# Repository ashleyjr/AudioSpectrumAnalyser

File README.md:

AudioSpectrumAnalyser
=====================

20Hz - 20KHz spectrum analyser which will eventually be part of hi-fi system. Processing on a beefy microcontroller and a small display with spectrum grpah.

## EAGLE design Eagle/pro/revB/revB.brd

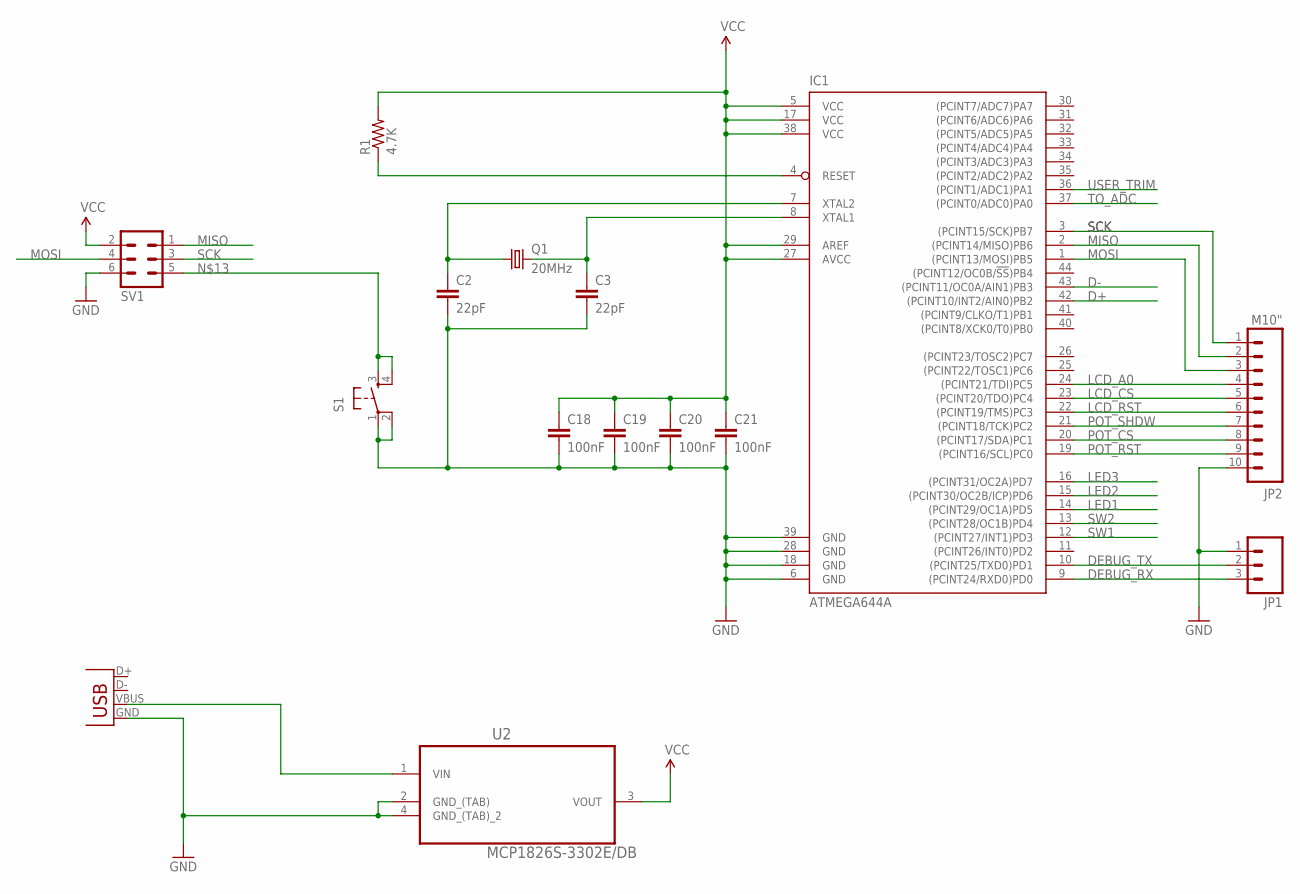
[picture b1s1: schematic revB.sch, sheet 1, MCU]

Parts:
C2, C3: 22pF; 0805
C18, C19, C20, C21: 100nF; 0805
IC1: ATMEGA644A; TQFP44
JP1: M03PTH; 1X03
JP2: M10"; 1X10
Q1: 20MHz; HC49U-V
R1: 4.7K; 1206
S1: TAC_SWITCHPTH; TACTILE-PTH
SV1: MA03-2
U2: MCP1826S-3302E/DB; SOT230P700X180-4N
X2: USB-MB-H

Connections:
D+: IC1.42 ((PCINT10/INT2/AIN0)PB2)
D-: IC1.43 ((PCINT11/OC0A/AIN1)PB3)
DEBUG_RX: IC1.9 ((PCINT24/RXD0)PD0), JP1.3
DEBUG_TX: IC1.10 ((PCINT25/TXD0)PD1), JP1.2
GND: C2.2, C3.2, C18.2, C19.2, C20.2, C21.2, IC1.6 (GND), IC1.18 (GND), IC1.28 (GND), IC1.39 (GND), JP1.1, JP2.10, S1.1, S1.2, SV1.6, U2.2 (GND_(TAB)), U2.4 (GND_(TAB)_2), X2.GND; also elsewhere on the board
LCD_A0: IC1.24 ((PCINT21/TDI)PC5), JP2.4; also elsewhere on the board
LCD_CS: IC1.23 ((PCINT20/TDO)PC4), JP2.5; also elsewhere on the board
LCD_RST: IC1.22 ((PCINT19/TMS)PC3), JP2.6; also elsewhere on the board
LED1: IC1.14 ((PCINT29/OC1A)PD5); also elsewhere on the board
LED2: IC1.15 ((PCINT30/OC2B/ICP)PD6); also elsewhere on the board
LED3: IC1.16 ((PCINT31/OC2A)PD7); also elsewhere on the board
MISO: IC1.2 ((PCINT14/MISO)PB6), JP2.2, SV1.1; also elsewhere on the board
MOSI: IC1.1 ((PCINT13/MOSI)PB5), JP2.3, SV1.4; also elsewhere on the board
unnamed: C3.1, IC1.8 (XTAL1), Q1.2
unnamed: C2.1, IC1.7 (XTAL2), Q1.1
unnamed: S1.3, S1.4, SV1.5
unnamed: U2.1 (VIN), X2.VBUS
POT_CS: IC1.20 ((PCINT17/SDA)PC1), JP2.8; also elsewhere on the board
POT_RST: IC1.19 ((PCINT16/SCL)PC0), JP2.9; also elsewhere on the board
POT_SHDW: IC1.21 ((PCINT18/TCK)PC2), JP2.7; also elsewhere on the board
RESET: IC1.4 (RESET), R1.1
SCK: IC1.3 ((PCINT15/SCK)PB7), JP2.1, SV1.3; also elsewhere on the board
SW1: IC1.12 ((PCINT27/INT1)PD3); also elsewhere on the board
SW2: IC1.13 ((PCINT28/OC1B)PD4); also elsewhere on the board
TO_ADC: IC1.37 ((PCINT0/ADC0)PA0); also elsewhere on the board
USER_TRIM: IC1.36 ((PCINT1/ADC1)PA1); also elsewhere on the board
VCC: C18.1, C19.1, C20.1, C21.1, IC1.5 (VCC), IC1.17 (VCC), IC1.27 (AVCC), IC1.29 (AREF), IC1.38 (VCC), R1.2, SV1.2, U2.3 (VOUT); also elsewhere on the board

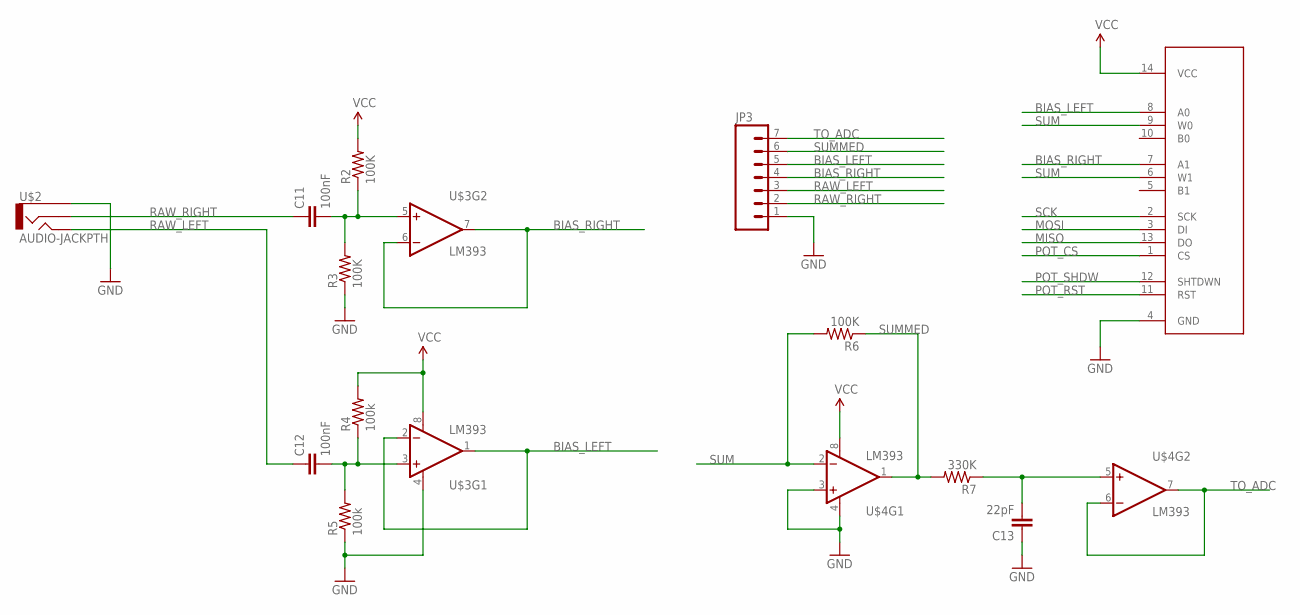
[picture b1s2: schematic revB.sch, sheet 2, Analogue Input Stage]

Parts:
C11, C12: 100nF; 0805
C13: 22pF; 0805
JP3: M07; 1X07
R2, R3, R6: 100K; 1206
R4, R5: 100k; 1206
R7: 330K; 1206
U1: MCP42XXX; SO014
U$2: AUDIO-JACKPTH; AUDIO-JACK
U$3, U$4: LM393; SO08

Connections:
BIAS_LEFT: JP3.5, U1.8 (A0), U$3.1 (OUT), U$3.2 (-IN)
BIAS_RIGHT: JP3.4, U1.7 (A1), U$3.6 (-IN), U$3.7 (OUT)
GND: C13.1, JP3.1, R3.1, R5.1, U1.4 (GND), U$2.1, U$3.4 (V-), U$4.3 (+IN), U$4.4 (V-); also elsewhere on the board
MISO: U1.13 (DO); also elsewhere on the board
MOSI: U1.3 (DI); also elsewhere on the board
unnamed: C11.2, R2.1, R3.2, U$3.5 (+IN)
unnamed: C12.2, R4.1, R5.2, U$3.3 (+IN)
unnamed: C13.2, R7.1, U$4.5 (+IN)
POT_CS: U1.1 (CS); also elsewhere on the board
POT_RST: U1.11 (RST); also elsewhere on the board
POT_SHDW: U1.12 (SHTDWN); also elsewhere on the board
RAW_LEFT: C12.1, JP3.3, U$2.5
RAW_RIGHT: C11.1, JP3.2, U$2.2
SCK: U1.2 (SCK); also elsewhere on the board
SUM: R6.2, U1.6 (W1), U1.9 (W0), U$4.2 (-IN)
SUMMED: JP3.6, R6.1, R7.2, U$4.1 (OUT)
TO_ADC: JP3.7, U$4.6 (-IN), U$4.7 (OUT); also elsewhere on the board
VCC: R2.2, R4.2, U1.14 (VCC), U$3.8 (V+), U$4.8 (V+); also elsewhere on the board

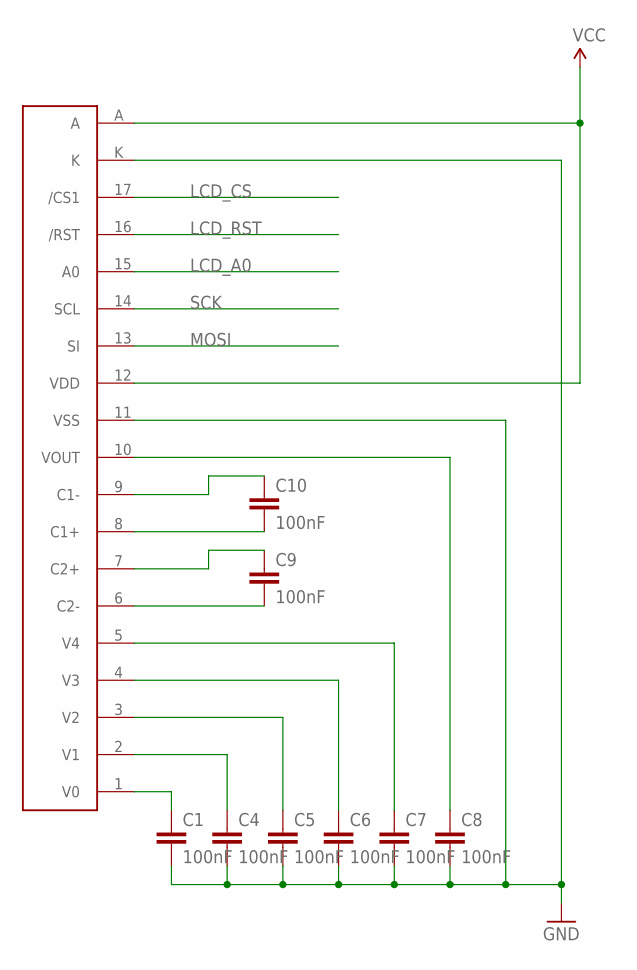
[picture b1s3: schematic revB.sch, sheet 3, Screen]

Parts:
C1, C4, C5, C6, C7, C8, C9, C10: 100nF; 0805
U$1: NHD_128X32

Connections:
GND: C1.2, C4.2, C5.2, C6.2, C7.2, C8.2, U$1.11 (VSS), U$1.K; also elsewhere on the board
LCD_A0: U$1.15 (A0); also elsewhere on the board
LCD_CS: U$1.17 (/CS1); also elsewhere on the board
LCD_RST: U$1.16 (/RST); also elsewhere on the board
MOSI: U$1.13 (SI); also elsewhere on the board
unnamed: C9.2, U$1.6 (C2-)
unnamed: C9.1, U$1.7 (C2+)
unnamed: C10.2, U$1.8 (C1+)
unnamed: C10.1, U$1.9 (C1-)
unnamed: C1.1, U$1.1 (V0)
unnamed: C4.1, U$1.2 (V1)
unnamed: C5.1, U$1.3 (V2)
unnamed: C6.1, U$1.4 (V3)
unnamed: C7.1, U$1.5 (V4)
unnamed: C8.1, U$1.10 (VOUT)
SCK: U$1.14 (SCL); also elsewhere on the board
VCC: U$1.12 (VDD), U$1.A; also elsewhere on the board

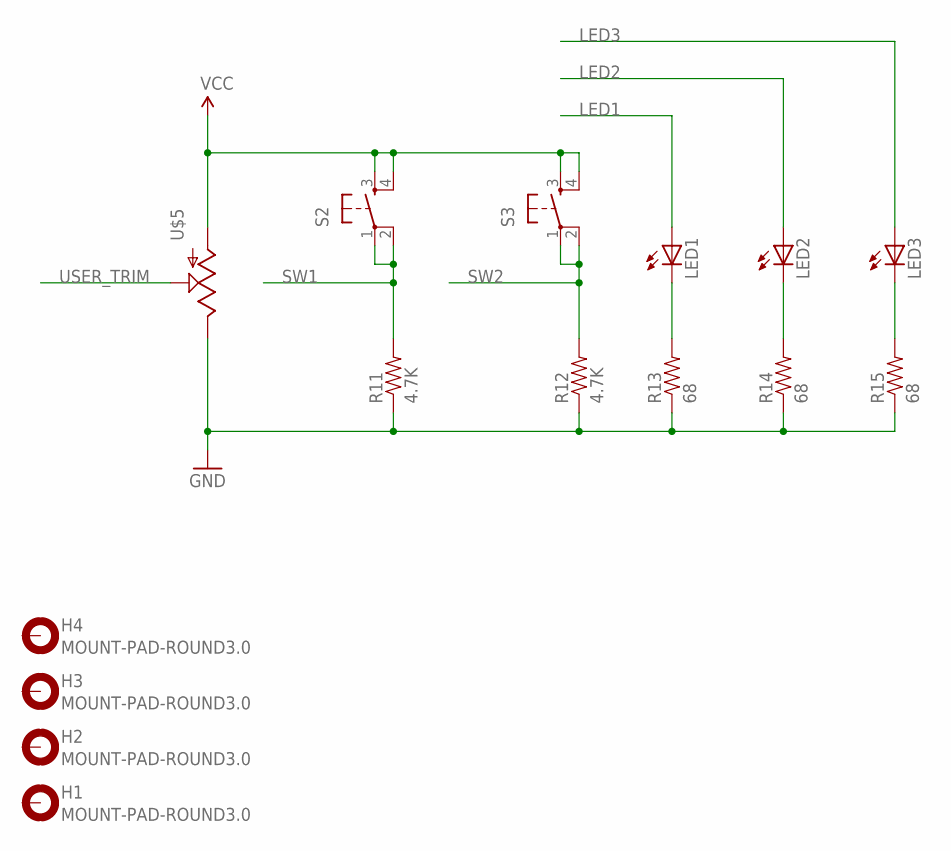
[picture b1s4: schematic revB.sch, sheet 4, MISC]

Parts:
H1, H2, H3, H4: MOUNT-PAD-ROUND3.0; 3,0-PAD
LED1, LED2, LED3: LED1206; LED-1206
R11, R12: 4.7K; 1206
R13, R14, R15: 68; 1206
S2, S3: TAC_SWITCHPTH; TACTILE-PTH
U$5: POTTRIM; TRIM_POT

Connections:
GND: R11.1, R12.1, R13.1, R14.1, R15.1, U$5.2 (E); also elsewhere on the board
LED1: LED1.A; also elsewhere on the board
LED2: LED2.A; also elsewhere on the board
LED3: LED3.A; also elsewhere on the board
unnamed: LED1.C, R13.2
unnamed: LED2.C, R14.2
unnamed: LED3.C, R15.2
SW1: R11.2, S2.1, S2.2; also elsewhere on the board
SW2: R12.2, S3.1, S3.2; also elsewhere on the board
USER_TRIM: U$5.1 (S); also elsewhere on the board
VCC: S2.3, S2.4, S3.3, S3.4, U$5.3 (A); also elsewhere on the board

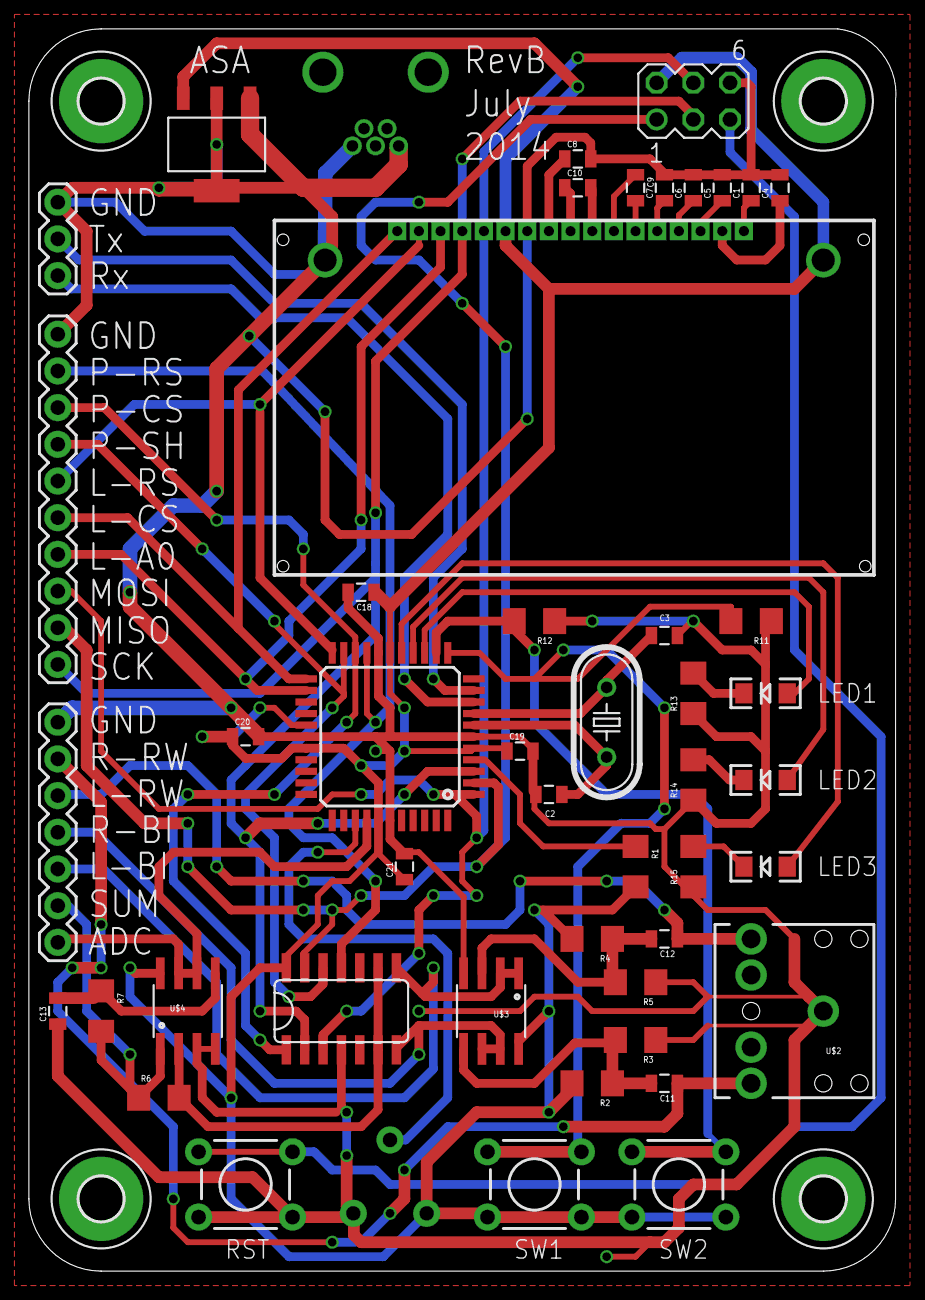
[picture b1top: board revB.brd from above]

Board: 2 copper layers, 60.0 x 86.0 mm, 53 parts (0 on the bottom side), 47 nets.

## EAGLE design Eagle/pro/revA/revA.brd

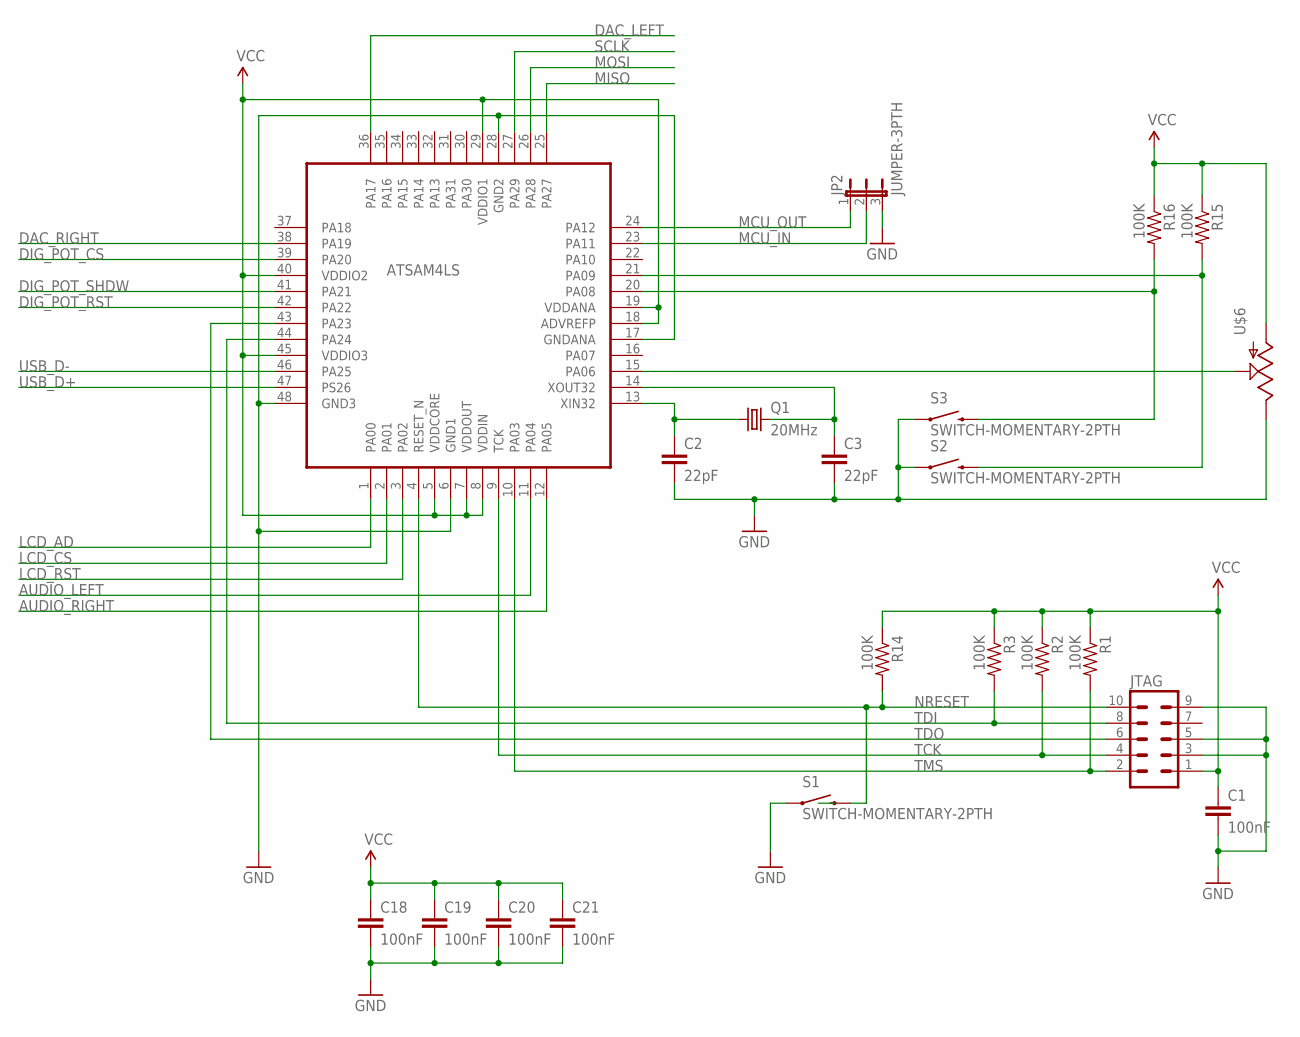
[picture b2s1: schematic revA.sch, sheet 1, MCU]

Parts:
ATSAM4LS: ATSAM4LSAA-AUR; TQFP48
C1, C18, C19, C20, C21: 100nF; 0805
C2, C3: 22pF; 0805
JP2: JUMPER-3PTH; 1X03
JTAG: MA05-2
Q1: 20MHz; HC49U-V
R1, R2, R3, R14, R15, R16: 100K; 1206
S1, S2, S3: SWITCH-MOMENTARY-2PTH; TACTILE-PTH
U$6: POTTRIM; TRIM_POT

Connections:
AUDIO_LEFT: ATSAM4LS.11 (PA04); also elsewhere on the board
AUDIO_RIGHT: ATSAM4LS.12 (PA05); also elsewhere on the board
DAC_LEFT: ATSAM4LS.36 (PA17); also elsewhere on the board
DAC_RIGHT: ATSAM4LS.38 (PA19); also elsewhere on the board
DIG_POT_CS: ATSAM4LS.39 (PA20); also elsewhere on the board
DIG_POT_RST: ATSAM4LS.42 (PA22); also elsewhere on the board
DIG_POT_SHDW: ATSAM4LS.41 (PA21); also elsewhere on the board
GND: ATSAM4LS.6 (GND1), ATSAM4LS.17 (GNDANA), ATSAM4LS.28 (GND2), ATSAM4LS.48 (GND3), C1.2, C2.2, C3.2, C18.2, C19.2, C20.2, C21.2, JP2.3, JTAG.3, JTAG.5, JTAG.9, S1.1, S2.1, S3.1, U$6.2 (E); also elsewhere on the board
LCD_AD: ATSAM4LS.1 (PA00); also elsewhere on the board
LCD_CS: ATSAM4LS.2 (PA01); also elsewhere on the board
LCD_RST: ATSAM4LS.3 (PA02); also elsewhere on the board
MCU_IN: ATSAM4LS.23 (PA11), JP2.2
MCU_OUT: ATSAM4LS.24 (PA12), JP2.1
MISO: ATSAM4LS.25 (PA27); also elsewhere on the board
MOSI: ATSAM4LS.26 (PA28); also elsewhere on the board
unnamed: ATSAM4LS.14 (XOUT32), C3.1, Q1.2
unnamed: ATSAM4LS.13 (XIN32), C2.1, Q1.1
unnamed: ATSAM4LS.15 (PA06), U$6.1 (S)
unnamed: ATSAM4LS.21 (PA09), R15.2, S2.3 (2)
unnamed: ATSAM4LS.20 (PA08), R16.2, S3.3 (2)
NRESET: ATSAM4LS.4 (RESET_N), JTAG.10, R14.2, S1.3 (2)
SCLK: ATSAM4LS.27 (PA29); also elsewhere on the board
TCK: ATSAM4LS.9 (TCK), JTAG.4, R2.2
TDI: ATSAM4LS.44 (PA24), JTAG.8, R3.2
TDO: ATSAM4LS.43 (PA23), JTAG.6
TMS: ATSAM4LS.10 (PA03), JTAG.2, R1.2
USB_D+: ATSAM4LS.47 (PS26); also elsewhere on the board
USB_D-: ATSAM4LS.46 (PA25); also elsewhere on the board
VCC: ATSAM4LS.5 (VDDCORE), ATSAM4LS.7 (VDDOUT), ATSAM4LS.8 (VDDIN), ATSAM4LS.18 (ADVREFP), ATSAM4LS.19 (VDDANA), ATSAM4LS.29 (VDDIO1), ATSAM4LS.40 (VDDIO2), ATSAM4LS.45 (VDDIO3), C1.1, C18.1, C19.1, C20.1, C21.1, JTAG.1, R1.1, R2.1, R3.1, R14.1, R15.1, R16.1, U$6.3 (A); also elsewhere on the board

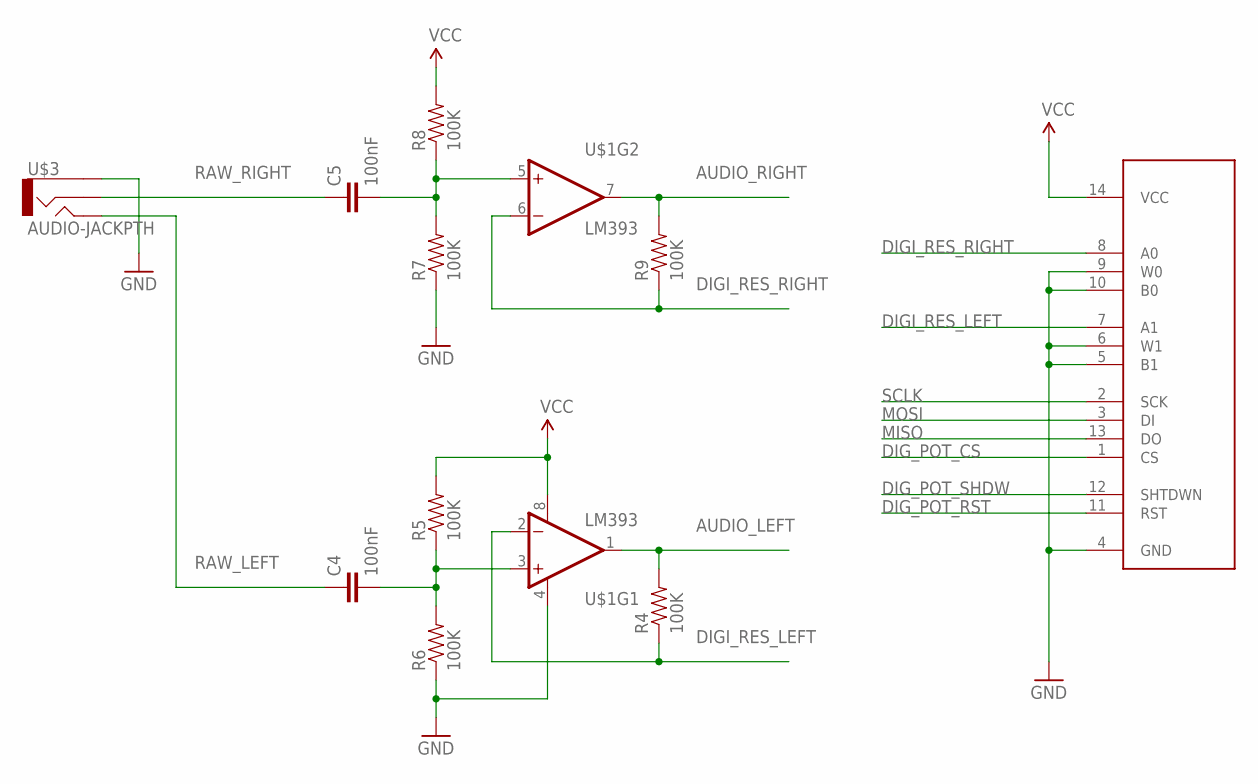
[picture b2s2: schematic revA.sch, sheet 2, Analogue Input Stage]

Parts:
C4, C5: 100nF; 0805
R4, R5, R6, R7, R8, R9: 100K; 1206
U1: MCP42XXX; SO014
U$1: LM393; SO08
U$3: AUDIO-JACKPTH; AUDIO-JACK

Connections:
AUDIO_LEFT: R4.2, U$1.1 (OUT); also elsewhere on the board
AUDIO_RIGHT: R9.2, U$1.7 (OUT); also elsewhere on the board
DIGI_RES_LEFT: R4.1, U1.7 (A1), U$1.2 (-IN)
DIGI_RES_RIGHT: R9.1, U1.8 (A0), U$1.6 (-IN)
DIG_POT_CS: U1.1 (CS); also elsewhere on the board
DIG_POT_RST: U1.11 (RST); also elsewhere on the board
DIG_POT_SHDW: U1.12 (SHTDWN); also elsewhere on the board
GND: R6.1, R7.1, U1.4 (GND), U1.5 (B1), U1.6 (W1), U1.9 (W0), U1.10 (B0), U$1.4 (V-), U$3.1; also elsewhere on the board
MISO: U1.13 (DO); also elsewhere on the board
MOSI: U1.3 (DI); also elsewhere on the board
unnamed: C5.2, R7.2, R8.1, U$1.5 (+IN)
unnamed: C4.2, R5.1, R6.2, U$1.3 (+IN)
RAW_LEFT: C4.1, U$3.5
RAW_RIGHT: C5.1, U$3.2
SCLK: U1.2 (SCK); also elsewhere on the board
VCC: R5.2, R8.2, U1.14 (VCC), U$1.8 (V+); also elsewhere on the board

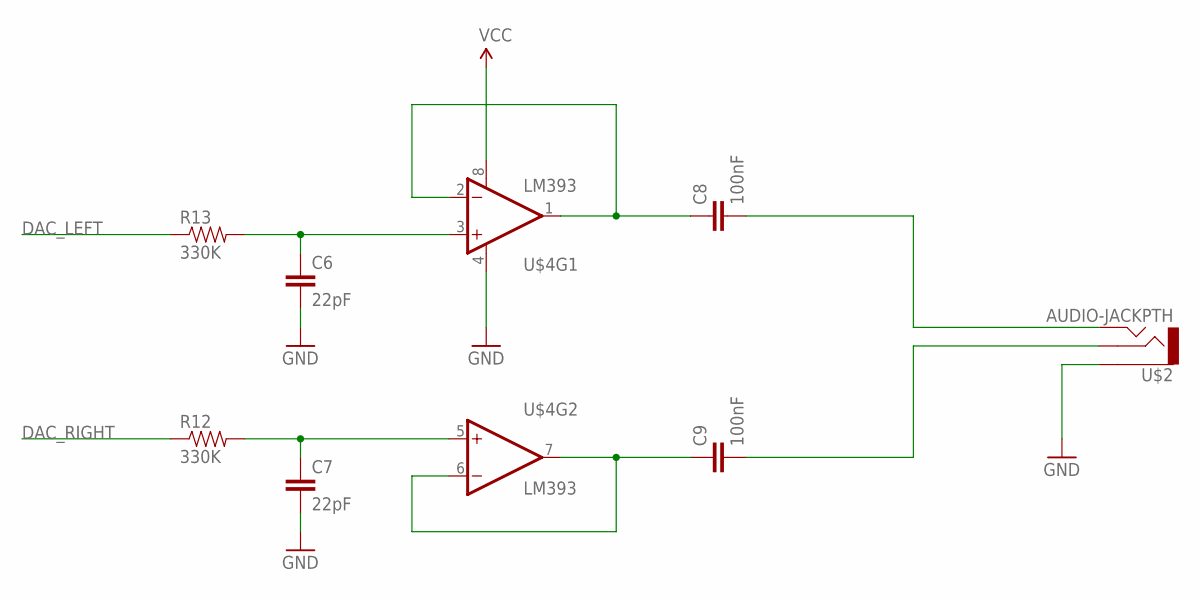
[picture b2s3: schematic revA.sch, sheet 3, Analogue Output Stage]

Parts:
C6, C7: 22pF; 0805
C8, C9: 100nF; 0805
R12, R13: 330K; 1206
U$2: AUDIO-JACKPTH; AUDIO-JACK
U$4: LM393; SO08

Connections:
DAC_LEFT: R13.1; also elsewhere on the board
DAC_RIGHT: R12.1; also elsewhere on the board
GND: C6.2, C7.2, U$2.1, U$4.4 (V-); also elsewhere on the board
unnamed: C9.1, U$4.6 (-IN), U$4.7 (OUT)
unnamed: C9.2, U$2.2
unnamed: C8.1, U$4.1 (OUT), U$4.2 (-IN)
unnamed: C6.1, R13.2, U$4.3 (+IN)
unnamed: C7.1, R12.2, U$4.5 (+IN)
unnamed: C8.2, U$2.5
VCC: U$4.8 (V+); also elsewhere on the board

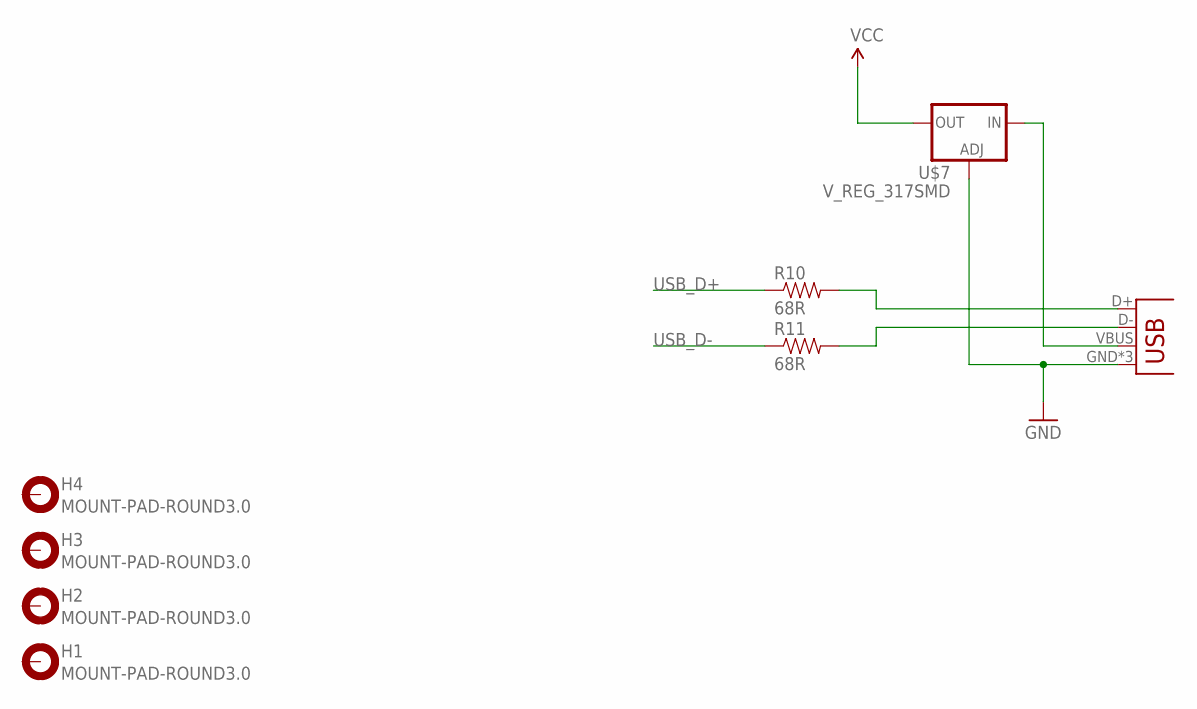
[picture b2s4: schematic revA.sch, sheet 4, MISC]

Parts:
H1, H2, H3, H4: MOUNT-PAD-ROUND3.0; 3,0-PAD
JP1: USB-MICROB
R10, R11: 68R; 1206
U$7: V_REG_317SMD; SOT223

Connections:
GND: JP1.GND, JP1.MT1 (GND), JP1.MT2 (GND), U$7.1 (ADJ); also elsewhere on the board
unnamed: JP1.D-, R11.2
unnamed: JP1.D+, R10.2
unnamed: JP1.VBUS, U$7.3 (IN)
USB_D+: R10.1; also elsewhere on the board
USB_D-: R11.1; also elsewhere on the board
VCC: U$7.2 (OUT); also elsewhere on the board

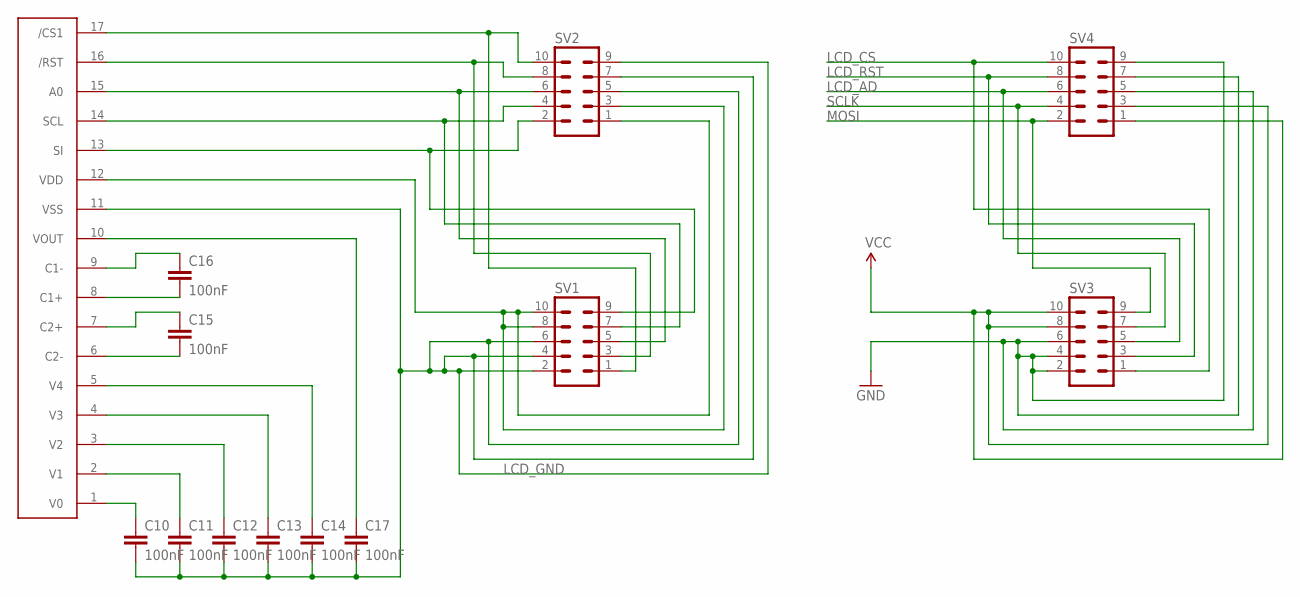
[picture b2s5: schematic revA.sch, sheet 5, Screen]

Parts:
C10, C11, C12, C13, C14, C15, C16, C17: 100nF; 0805
SV1, SV2, SV3, SV4: MA05-2
U$5: NHD_128X32

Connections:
GND: SV3.2, SV3.4, SV3.6, SV4.5, SV4.7, SV4.9; also elsewhere on the board
LCD_AD: SV3.5, SV4.6; also elsewhere on the board
LCD_CS: SV3.1, SV4.10; also elsewhere on the board
LCD_GND: C10.2, C11.2, C12.2, C13.2, C14.2, C17.2, SV1.2, SV1.4, SV1.6, SV2.5, SV2.7, SV2.9, U$5.11 (VSS)
LCD_RST: SV3.3, SV4.8; also elsewhere on the board
MOSI: SV3.9, SV4.2; also elsewhere on the board
unnamed: C10.1, U$5.1 (V0)
unnamed: C11.1, U$5.2 (V1)
unnamed: C12.1, U$5.3 (V2)
unnamed: C13.1, U$5.4 (V3)
unnamed: C14.1, U$5.5 (V4)
unnamed: SV1.8, SV1.10, SV2.1, SV2.3, U$5.12 (VDD)
unnamed: C15.2, U$5.6 (C2-)
unnamed: C15.1, U$5.7 (C2+)
unnamed: C16.2, U$5.8 (C1+)
unnamed: C16.1, U$5.9 (C1-)
unnamed: C17.1, U$5.10 (VOUT)
unnamed: SV1.1, SV2.10, U$5.17 (/CS1)
unnamed: SV1.3, SV2.8, U$5.16 (/RST)
unnamed: SV1.5, SV2.6, U$5.15 (A0)
unnamed: SV1.7, SV2.4, U$5.14 (SCL)
unnamed: SV1.9, SV2.2, U$5.13 (SI)
SCLK: SV3.7, SV4.4; also elsewhere on the board
VCC: SV3.8, SV3.10, SV4.1, SV4.3; also elsewhere on the board

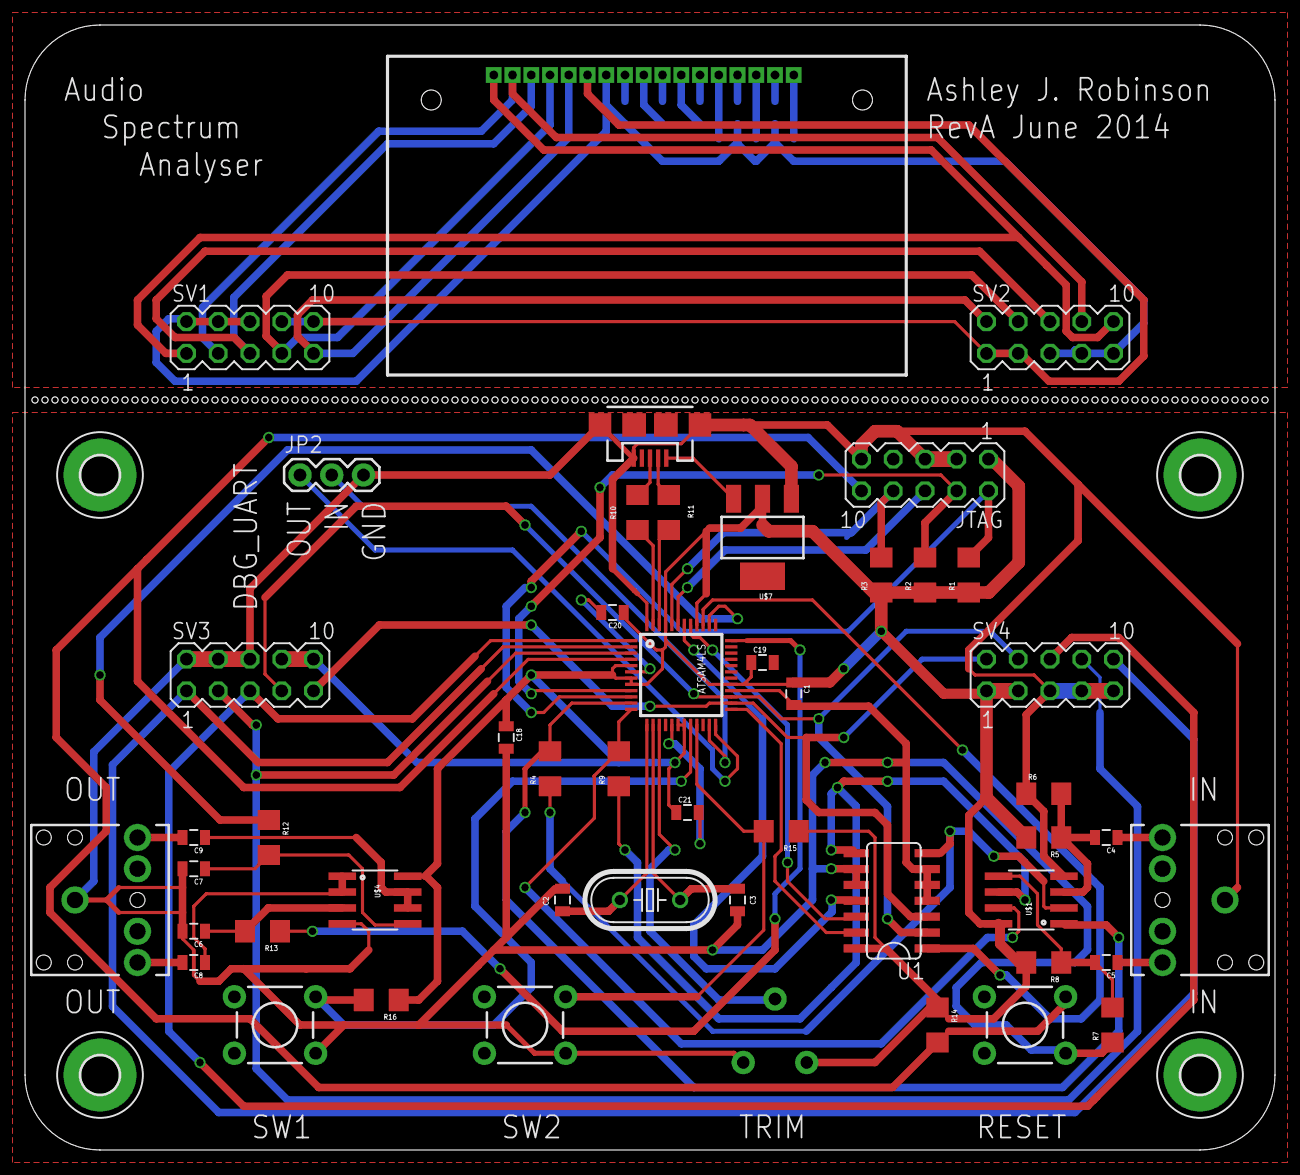
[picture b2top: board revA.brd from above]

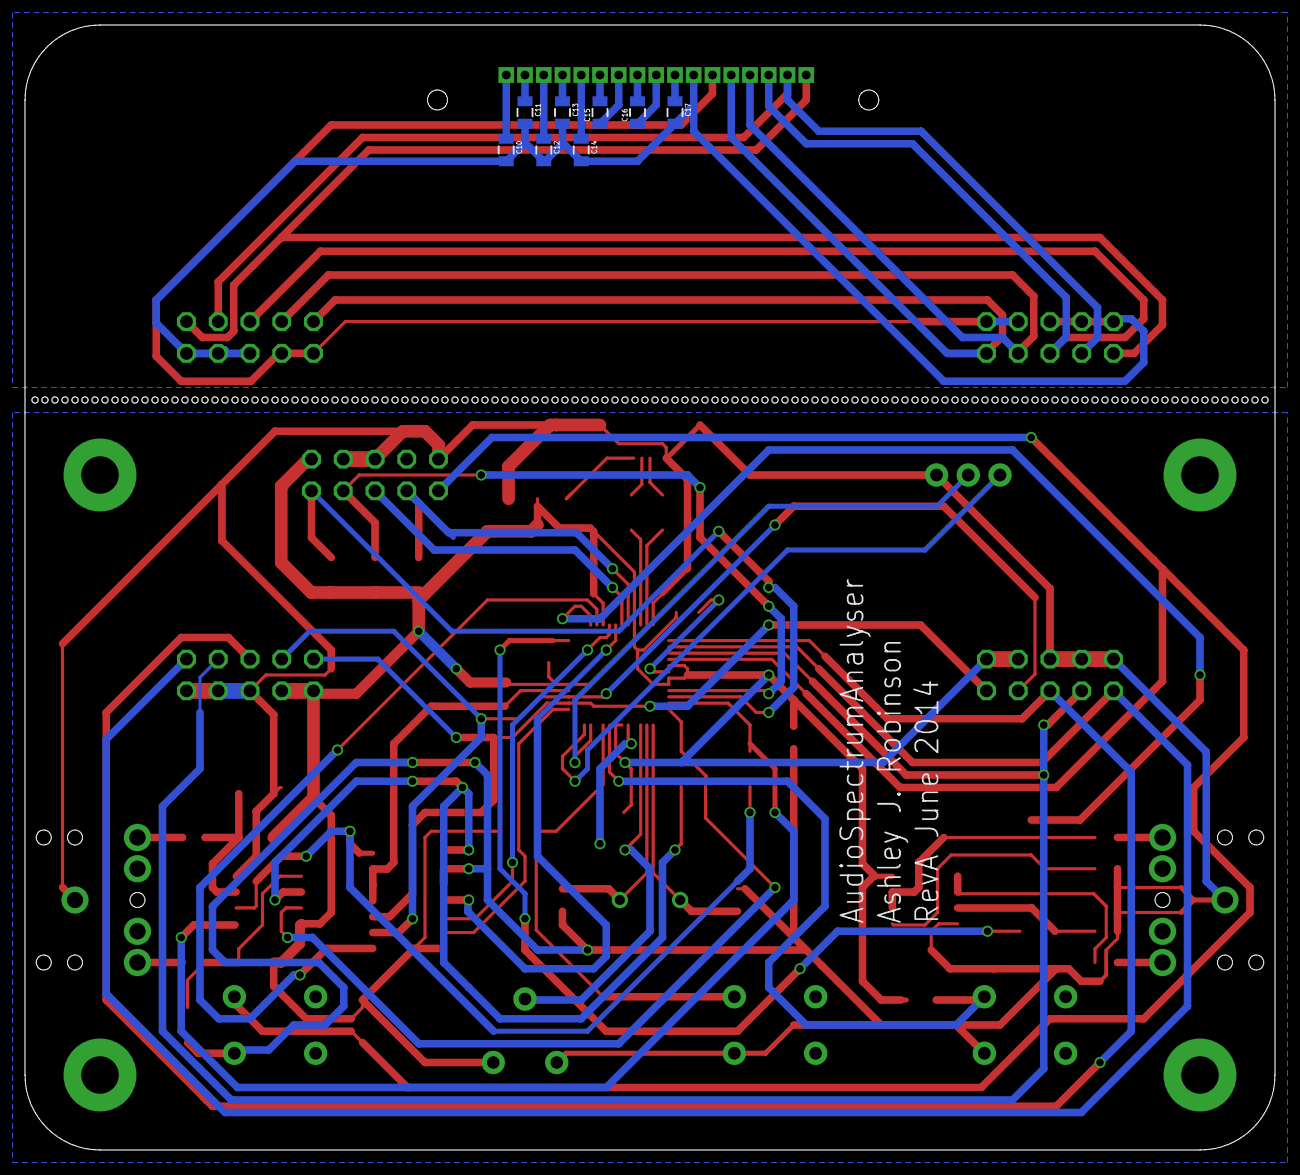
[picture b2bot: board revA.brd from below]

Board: 2 copper layers, 100.0 x 90.0 mm, 61 parts (8 on the bottom side), 61 nets.

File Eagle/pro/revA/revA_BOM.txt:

Partlist exported from C:/Users/Ashley/Desktop/AudioSpectrumAnalyser/Eagle/pro/revA/revA.sch at 17/06/2014 20:33:24

Part     Value                 Device                Package     Description         MF MPN OC_FARNELL OC_NEWARK PROD_ID   
ATSAM4LS ATSAM4LSAA-AUR        ATSAM4LSAA-AUR        TQFP48                                                                
C1       100nF                 CAP0805               0805        Capacitor                                                 
C2       22pF                  CAP0805               0805        Capacitor                                                 
C3       22pF                  CAP0805               0805        Capacitor                                                 
C4       100nF                 CAP0805               0805        Capacitor                                                 
C5       100nF                 CAP0805               0805        Capacitor                                                 
C6       22pF                  CAP0805               0805        Capacitor                                                 
C7       22pF                  CAP0805               0805        Capacitor                                                 
C8       100nF                 CAP0805               0805        Capacitor                                                 
C9       100nF                 CAP0805               0805        Capacitor                                                 
C10      100nF                 CAP0805               0805        Capacitor                                                 
C11      100nF                 CAP0805               0805        Capacitor                                                 
C12      100nF                 CAP0805               0805        Capacitor                                                 
C13      100nF                 CAP0805               0805        Capacitor                                                 
C14      100nF                 CAP0805               0805        Capacitor                                                 
C15      100nF                 CAP0805               0805        Capacitor                                                 
C16      100nF                 CAP0805               0805        Capacitor                                                 
C17      100nF                 CAP0805               0805        Capacitor                                                 
C18      100nF                 CAP0805               0805        Capacitor                                                 
C19      100nF                 CAP0805               0805        Capacitor                                                 
C20      100nF                 CAP0805               0805        Capacitor                                                 
C21      100nF                 CAP0805               0805        Capacitor                                                 
H1       MOUNT-PAD-ROUND3.0    MOUNT-PAD-ROUND3.0    3,0-PAD     MOUNTING PAD, round                                       
H2       MOUNT-PAD-ROUND3.0    MOUNT-PAD-ROUND3.0    3,0-PAD     MOUNTING PAD, round                                       
H3       MOUNT-PAD-ROUND3.0    MOUNT-PAD-ROUND3.0    3,0-PAD     MOUNTING PAD, round                                       
H4       MOUNT-PAD-ROUND3.0    MOUNT-PAD-ROUND3.0    3,0-PAD     MOUNTING PAD, round                                       
JP1      USB-MICROB            USB-MICROB            USB-MICROB  USB Connectors                                  CONN-09505
JP2      JUMPER-3PTH           JUMPER-3PTH           1X03                                                                  
JTAG                           MA05-2                MA05-2      PIN HEADER                 unknown    unknown             
Q1       20MHz                 CRYSTALHC49UV         HC49U-V     Crystals                                                  
R1       100K                  RESISTOR1206          1206        Resistor                                                  
R2       100K                  RESISTOR1206          1206        Resistor                                                  
R3       100K                  RESISTOR1206          1206        Resistor                                                  
R4       100K                  RESISTOR1206          1206        Resistor                                                  
R5       100K                  RESISTOR1206          1206        Resistor                                                  
R6       100K                  RESISTOR1206          1206        Resistor                                                  
R7       100K                  RESISTOR1206          1206        Resistor                                                  
R8       100K                  RESISTOR1206          1206        Resistor                                                  
R9       100K                  RESISTOR1206          1206        Resistor                                                  
R10      68R                   RESISTOR1206          1206        Resistor                                                  
R11      68R                   RESISTOR1206          1206        Resistor                                                  
R12      330K                  RESISTOR1206          1206        Resistor                                                  
R13      330K                  RESISTOR1206          1206        Resistor                                                  
R14      100K                  RESISTOR1206          1206        Resistor                                                  
R15      100K                  RESISTOR1206          1206        Resistor                                                  
R16      100K                  RESISTOR1206          1206        Resistor                                                  
S1       SWITCH-MOMENTARY-2PTH SWITCH-MOMENTARY-2PTH TACTILE-PTH                                                           
S2       SWITCH-MOMENTARY-2PTH SWITCH-MOMENTARY-2PTH TACTILE-PTH                                                           
S3       SWITCH-MOMENTARY-2PTH SWITCH-MOMENTARY-2PTH TACTILE-PTH                                                           
SV1                            MA05-2                MA05-2      PIN HEADER                 unknown    unknown             
SV2                            MA05-2                MA05-2      PIN HEADER                 unknown    unknown             
SV3                            MA05-2                MA05-2      PIN HEADER                 unknown    unknown             
SV4                            MA05-2                MA05-2      PIN HEADER                 unknown    unknown             
U$1      LM393                 LM393                 SO08                                                                  
U$2      AUDIO-JACKPTH         AUDIO-JACKPTH         AUDIO-JACK  3.5mm Audio Jack                                          
U$3      AUDIO-JACKPTH         AUDIO-JACKPTH         AUDIO-JACK  3.5mm Audio Jack                                          
U$4      LM393                 LM393                 SO08                                                                  
U$5      NHD_128X32            NHD_128X32            NHD_128X32                                                            
U$6      POTTRIM               POTTRIM               TRIM_POT                                                              
U$7      V_REG_317SMD          V_REG_317SMD          SOT223      Voltage Regulator                                         
U1       MCP42XXX              MCP42XXX              SO014

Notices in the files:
parts and their libraries:
SparkFun-Connectors: Licensing: Creative Commons ShareAlike 4.0 International - https://creativecommons.org/licenses/by-sa/4.0
